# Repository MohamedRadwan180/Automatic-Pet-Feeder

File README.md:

This report describes the design and construction of the prototype of a “Cat Automatic Feeder and Entertainer” carried out in Design Methodology and Mechatronics 1 subjects at VUB as part of the Bruface master of mechantronics at VUB and ULB universities. The idea is simple: building a device that can take care of a cat during a long weekend, taking care of their nutrition and mental health. It will be able to feed the pet the appropriate amount of food at feeding times. In addition, whenever necessary, it will provide an entertaining game to clear the cat's mind. The origin of this idea stems from the lack of a complete product in the market and the need for cat owners to be unconcerned about their cats for a few days. 

The design will consider every possible constraint to achieve all the objectives, such as safety and correct feeding. The building has been developed by laser-cutting for simple and flat parts pieces and 3D printing for more complex ones. The whole design has been carefully designed to consider the space requirements of all components. The materials have been chosen to achieve ecological and functional requirements. 

The electronics and programming subsystems have been implemented in an Arduino Uno, using different modules to take every signal and control the actuators when necessary. Every sensor and motor has been deeply researched to understand the required power supply and code to define the inputs and outputs. 

Every subsystem has been tested before being implemented into the general system. In this way, unique errors can be detected and solved.

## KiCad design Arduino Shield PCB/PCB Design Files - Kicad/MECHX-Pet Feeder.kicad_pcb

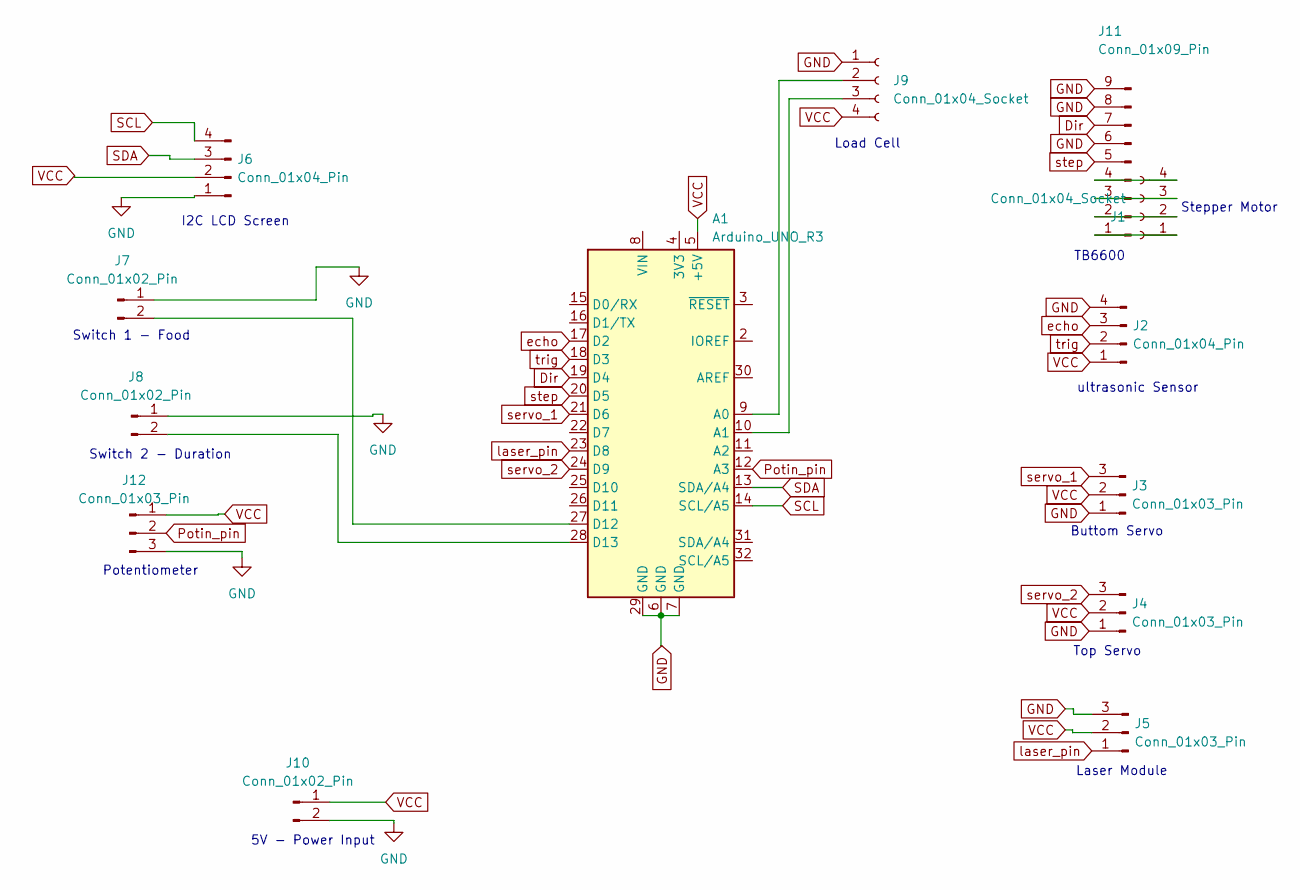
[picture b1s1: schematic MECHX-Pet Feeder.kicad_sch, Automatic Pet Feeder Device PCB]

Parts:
A1: Arduino_UNO_R3
J1: Conn_01x04_Socket; JST_EH_B4B-EH-A_1x04_P2.50mm_Vertical
J2, J6: Conn_01x04_Pin; PinHeader_1x04_P2.54mm_Vertical
J3, J4, J5, J12: Conn_01x03_Pin; PinHeader_1x03_P2.54mm_Vertical
J7, J8, J10: Conn_01x02_Pin; TerminalBlock_bornier-2_P5.08mm
J9: Conn_01x04_Socket; PinHeader_1x04_P2.54mm_Vertical
J11: Conn_01x09_Pin; PinHeader_1x09_P2.54mm_Vertical

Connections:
Dir: A1.19 (D4), J11.7
GND: A1.6 (GND), A1.7 (GND), A1.29 (GND), J2.4, J3.1, J4.1, J5.3, J6.1, J7.1, J8.1, J9.1, J10.2, J11.6, J11.8, J11.9, J12.3
unnamed: A1.9 (A0), J9.2
unnamed: A1.10 (A1), J9.3
unnamed: A1.27 (D12), J7.2
unnamed: A1.28 (D13), J8.2
unnamed: J1.1, J11.1
unnamed: J1.2, J11.2
unnamed: J1.3, J11.3
unnamed: J1.4, J11.4
Potin_pin: A1.12 (A3), J12.2
SCL: A1.14 (SCL/A5), J6.4
SDA: A1.13 (SDA/A4), J6.3
VCC: A1.5 (+5V), J2.1, J3.2, J4.2, J5.2, J6.2, J9.4, J10.1, J12.1
echo: A1.17 (D2), J2.3
laser_pin: A1.23 (D8), J5.1
servo_1: A1.21 (D6), J3.3
servo_2: A1.24 (D9), J4.3
step: A1.20 (D5), J11.5
trig: A1.18 (D3), J2.2

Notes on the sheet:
Switch 2 - Duration
5V - Power Input
Laser Module
Buttom Servo
Top Servo
Load Cell
I2C LCD Screen
ultrasonic Sensor
TB6600
Potentiometer
Stepper Motor
Switch 1 - Food

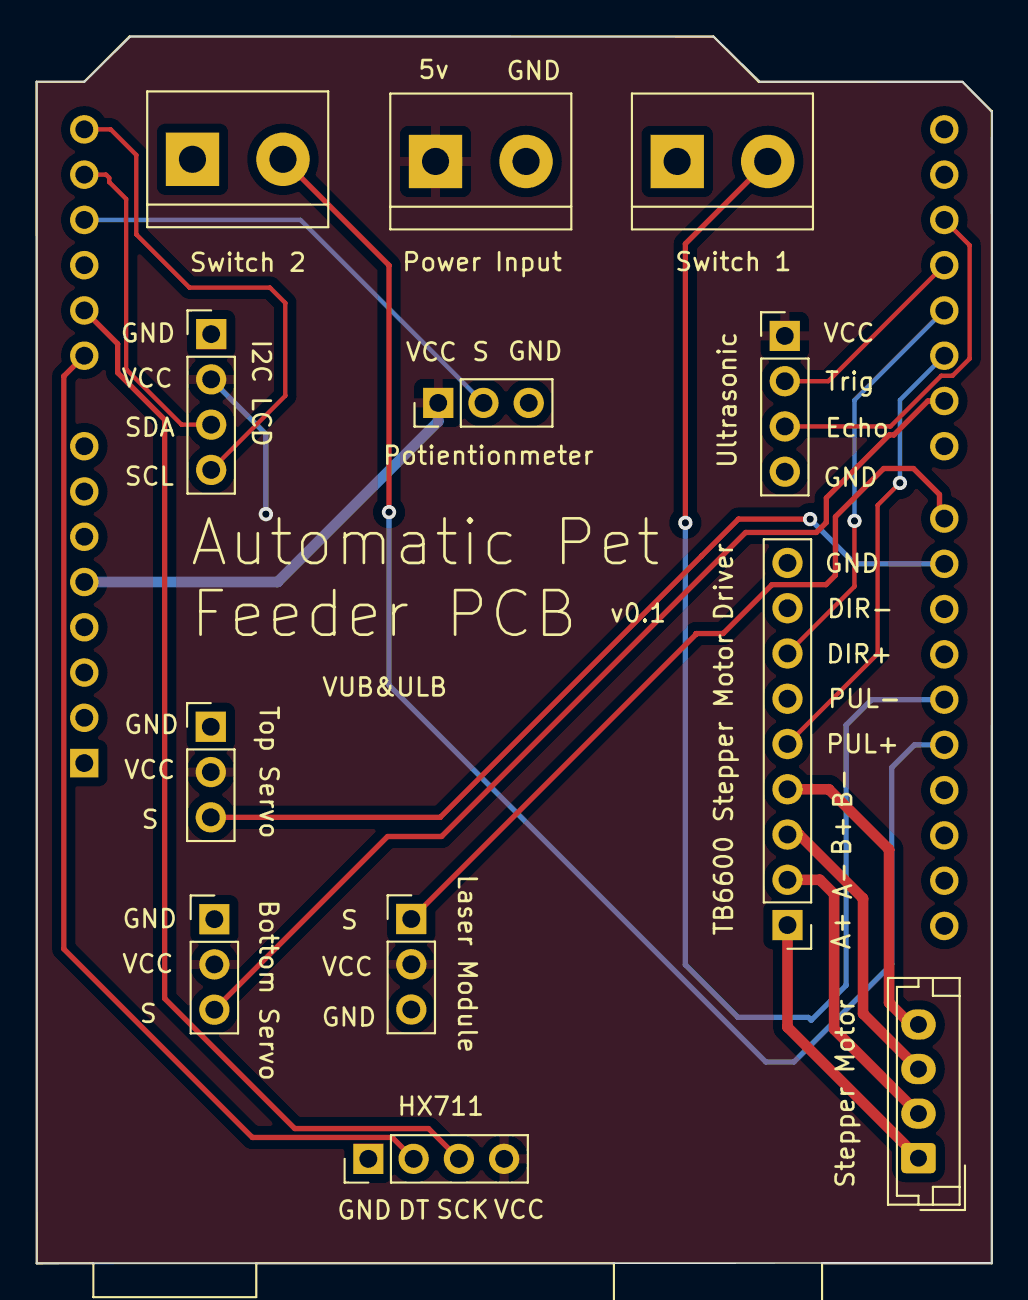
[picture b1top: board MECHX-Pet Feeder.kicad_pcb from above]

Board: 2 copper layers, 53.6 x 68.9 mm, 13 parts (0 on the bottom side), 20 nets.

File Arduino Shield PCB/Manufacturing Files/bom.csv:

Designator,Footprint,Quantity,Value,LCSC Part #
A1,Arduino_UNO_R3,1,Arduino_UNO_R3,
J1,JST_EH_B4B-EH-A_1x04_P2.50mm_Vertical,1,Conn_01x04_Socket,
"J10, J7, J8",TerminalBlock_bornier-2_P5.08mm,3,Conn_01x02_Pin,
J11,PinHeader_1x09_P2.54mm_Vertical,1,Conn_01x09_Pin,
"J12, J3, J4, J5",PinHeader_1x03_P2.54mm_Vertical,4,Conn_01x03_Pin,
"J2, J6",PinHeader_1x04_P2.54mm_Vertical,2,Conn_01x04_Pin,
J9,PinHeader_1x04_P2.54mm_Vertical,1,Conn_01x04_Socket,

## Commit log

2023-12-28 CAD Added
2023-12-28 Arduino Code
2023-12-28 Readme
